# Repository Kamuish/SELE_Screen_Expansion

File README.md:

# SCREEN EXPANSION PROJECT

The purpose of this project is to make two screens work as a single one, with the screen coming out of
the rigth screen, entering the left one. After "leaving" the left screen it should loop back.

We created a library to work with the LCD1602A LCD display, using the SPI and I2C communication protocols.
Afterwards, we implemented EEPROM,FLASH and SRAM memory tests to verify the proper behaviour of those memories.

If one of those memories fails, program execution shall be halted and an error message will appear on one of the screens.

## Project structure:

We have 3 different folders:

  - Board - where the schematic and PCB design are stored;
  - src - where the code is;
  - docs - where the documentation is stored.
  
# src structure:
  
  Inside this folder we find many folders, each for a different purpose:
  
    - I2C - folder in which we have a program to show the I2C protocol during the presentation;
    - SPI - folder in which we have a program to show the SPI protocol during the presentation;
    - SRAM - folder used for development of the SRAM test;
    - eeprom_write_hash - project used to write the hash to the eeprom memory address;
    - flash_test - folder used for the development of the Flash memory test;
    - hash_calc - python script to calculate the hash of a IntelHex file;
    - screen_expansion_project - the final project.
# The screen_expansion_project

Inside this folder the header files are inside the Header Files folder and the program files inside the Program Files folder.

All the files are properly named and commented, simplifying the task of reading the project's source files.

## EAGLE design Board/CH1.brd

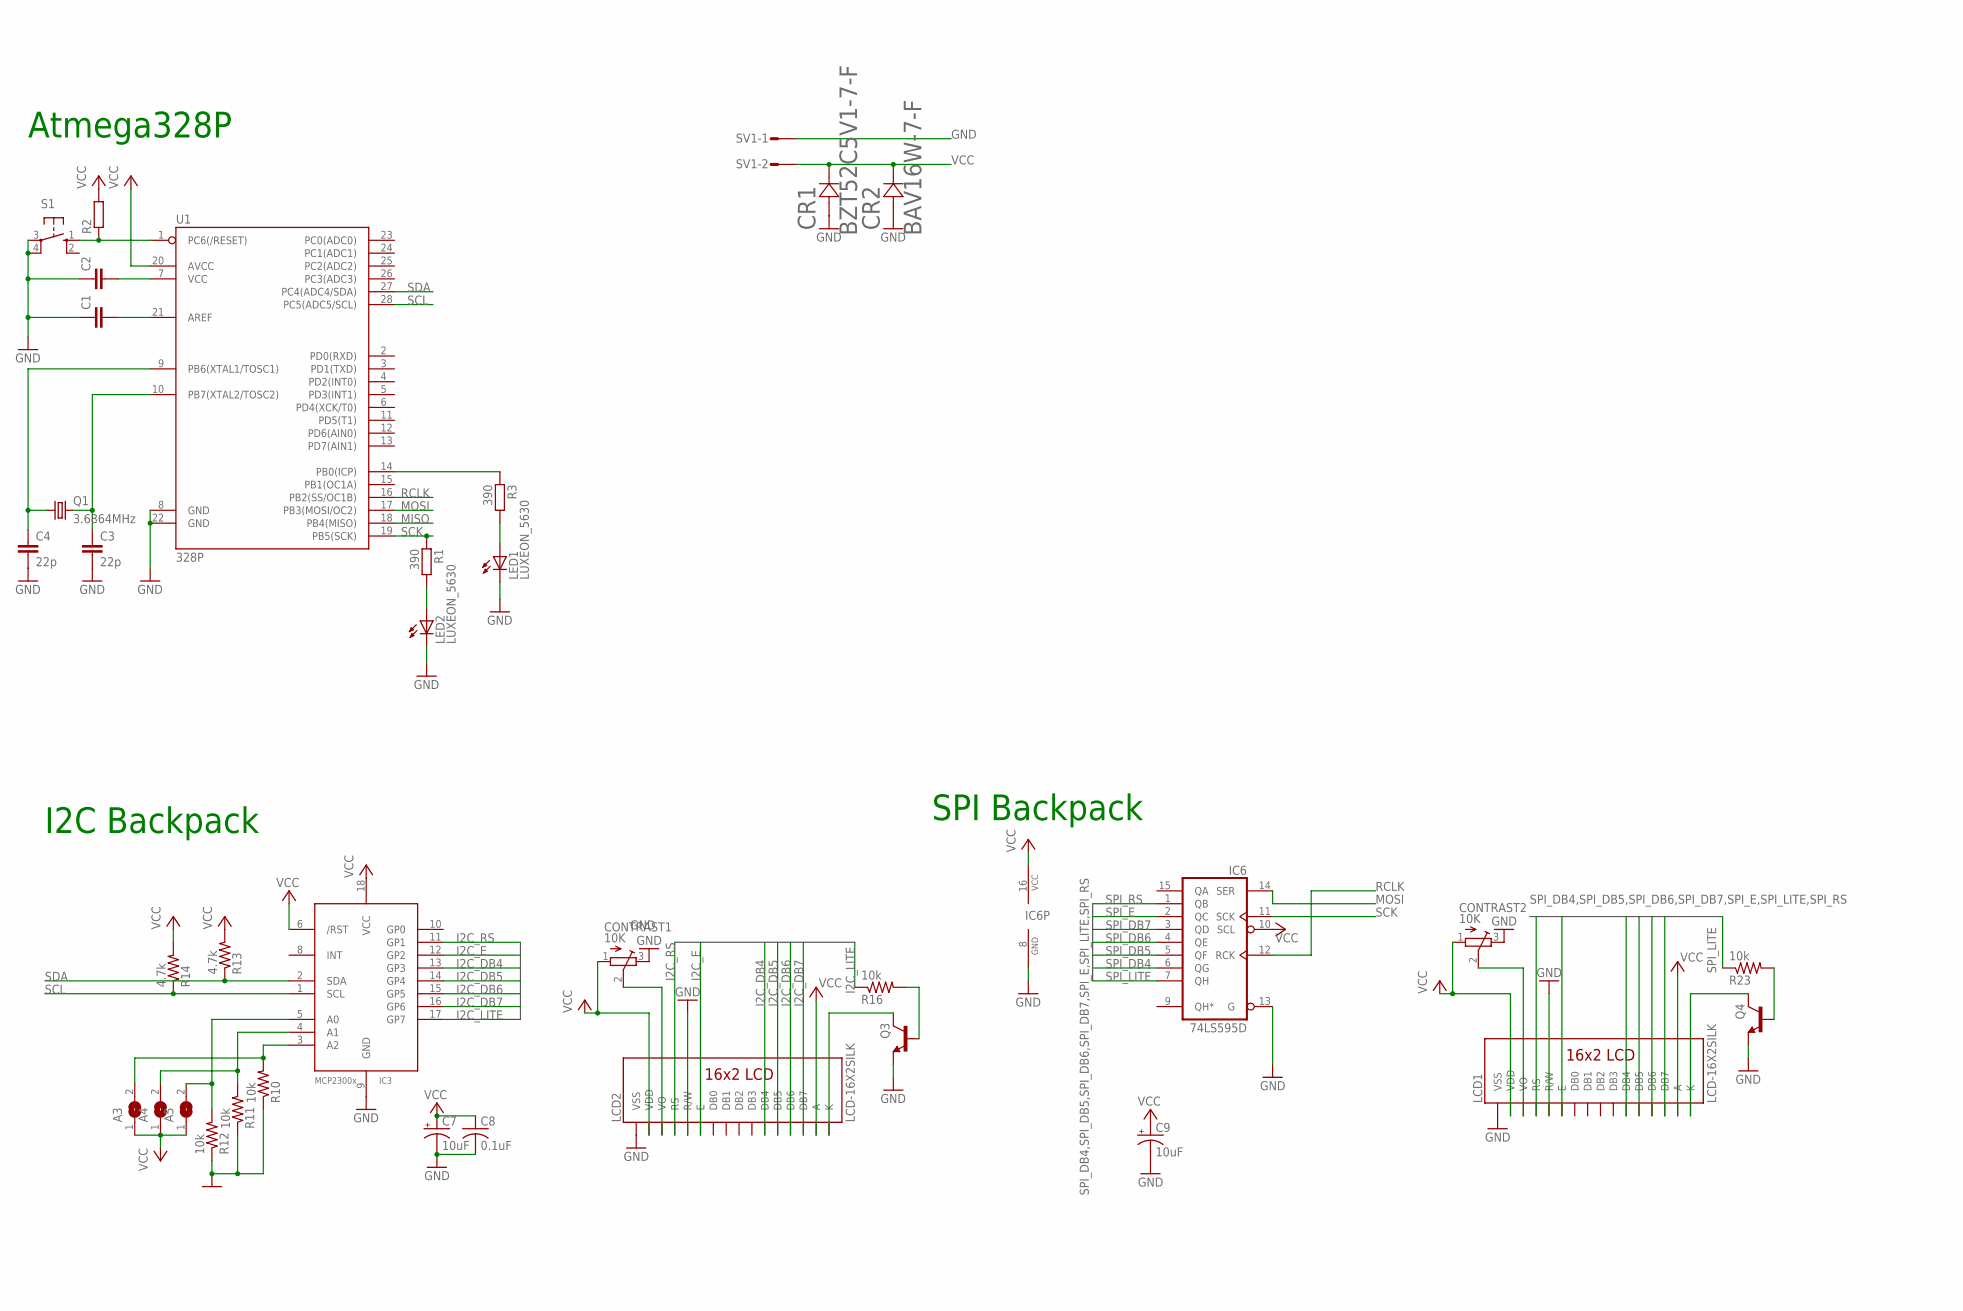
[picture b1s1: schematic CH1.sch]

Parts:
A3, A4, A5: SJ
C1, C2: C-EUC1206; C1206
C3, C4: 22p; C1206
C7, C9: 10uF; A/3216-18R
C8: 0.1uF; C0805K
CONTRAST1, CONTRAST2: 10K; TC33X
CR1: BZT52C5V1-7-F; SOD123
CR2: BAV16W-7-F; SOD123
IC3: MCP2300X/SO; SO18W
IC6: 74LS595D; SO16
LCD1, LCD2: LCD-16X2SILK; LCD-16X2
LED1, LED2: LUXEON_5630
Q1: 3.6864MHz; HC49/S
Q3, Q4: MMBT2222ALT1-NPN-SOT23-BEC; SOT23-BEC
R1, R3: 390; R1206
R2: R-EU_R1206; R1206
R10, R11, R12, R16, R23: 10k; R0805
R13, R14: 4.7k; R0805
S1: SWITCH-OMRON; SWITCH-OMRON_B3F-10XX
SV1: L02P
U1: 328P; MICROCONTROLLER_DIP28

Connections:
GND: C1.1, C2.1, C3.2, C4.2, C7.-, C8.2, C9.-, CONTRAST1.3 (E), CONTRAST2.3 (E), CR1.2 (21), CR2.2 (21), IC3.9 (GND), IC6.8 (GND), IC6.13 (G), LCD1.1 (VSS), LCD1.5 (R/W), LCD2.1 (VSS), LCD2.5 (R/W), LED1.1@1 (C), LED1.1@2 (C), LED2.1@1 (C), LED2.1@2 (C), Q3.E, Q4.E, R10.1, R11.1, R12.1, S1.3, S1.4 (P1), SV1.1, U1.8 (GND), U1.22 (GND)
I2C_DB4: IC3.13 (GP3), LCD2.11 (DB4)
I2C_DB5: IC3.14 (GP4), LCD2.12 (DB5)
I2C_DB6: IC3.15 (GP5), LCD2.13 (DB6)
I2C_DB7: IC3.16 (GP6), LCD2.14 (DB7)
I2C_E: IC3.12 (GP2), LCD2.6 (E)
I2C_LITE: IC3.17 (GP7), R16.1
I2C_RS: IC3.11 (GP1), LCD2.4 (RS)
MISO: U1.18 (PB4(MISO))
MOSI: IC6.14 (SER), U1.17 (PB3(MOSI/OC2))
unnamed: C3.1, Q1.2, U1.10 (PB7(XTAL2/TOSC2))
unnamed: C4.1, Q1.1, U1.9 (PB6(XTAL1/TOSC1))
unnamed: C2.2, U1.7 (VCC)
unnamed: C1.2, U1.21 (AREF)
unnamed: LED1.2 (A), R3.2
unnamed: LED2.2 (A), R1.2
unnamed: R2.1, S1.1 (S), U1.1 (PC6(/RESET))
unnamed: R3.1, U1.14 (PB0(ICP))
unnamed: A5.2, IC3.5 (A0), R12.2
unnamed: A4.2, IC3.4 (A1), R11.2
unnamed: A3.2, IC3.3 (A2), R10.2
unnamed: LCD2.16 (K), Q3.C
unnamed: Q3.B, R16.2
unnamed: CONTRAST1.2 (S), LCD2.3 (VO)
unnamed: LCD1.16 (K), Q4.C
unnamed: Q4.B, R23.2
unnamed: CONTRAST2.2 (S), LCD1.3 (VO)
RCLK: IC6.12 (RCK), U1.16 (PB2(SS/OC1B))
SCK: IC6.11 (SCK), R1.1, U1.19 (PB5(SCK))
SCL: IC3.1 (SCL), R14.1, U1.28 (PC5(ADC5/SCL))
SDA: IC3.2 (SDA), R13.1, U1.27 (PC4(ADC4/SDA))
SPI_DB4: IC6.6 (QG), LCD1.11 (DB4)
SPI_DB5: IC6.5 (QF), LCD1.12 (DB5)
SPI_DB6: IC6.4 (QE), LCD1.13 (DB6)
SPI_DB7: IC6.3 (QD), LCD1.14 (DB7)
SPI_E: IC6.2 (QC), LCD1.6 (E)
SPI_LITE: IC6.7 (QH), R23.1
SPI_RS: IC6.1 (QB), LCD1.4 (RS)
VCC: A3.1, A4.1, A5.1, C7.+, C8.1, C9.+, CONTRAST1.1 (A), CONTRAST2.1 (A), CR1.1 (12), CR2.1 (12), IC3.6 (/RST), IC3.18 (VCC), IC6.10 (SCL), IC6.16 (VCC), LCD1.2 (VDD), LCD1.15 (A), LCD2.2 (VDD), LCD2.15 (A), R2.2, R13.2, R14.2, SV1.2, U1.20 (AVCC)

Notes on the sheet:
Atmega328P
I2C Backpack
SPI Backpack

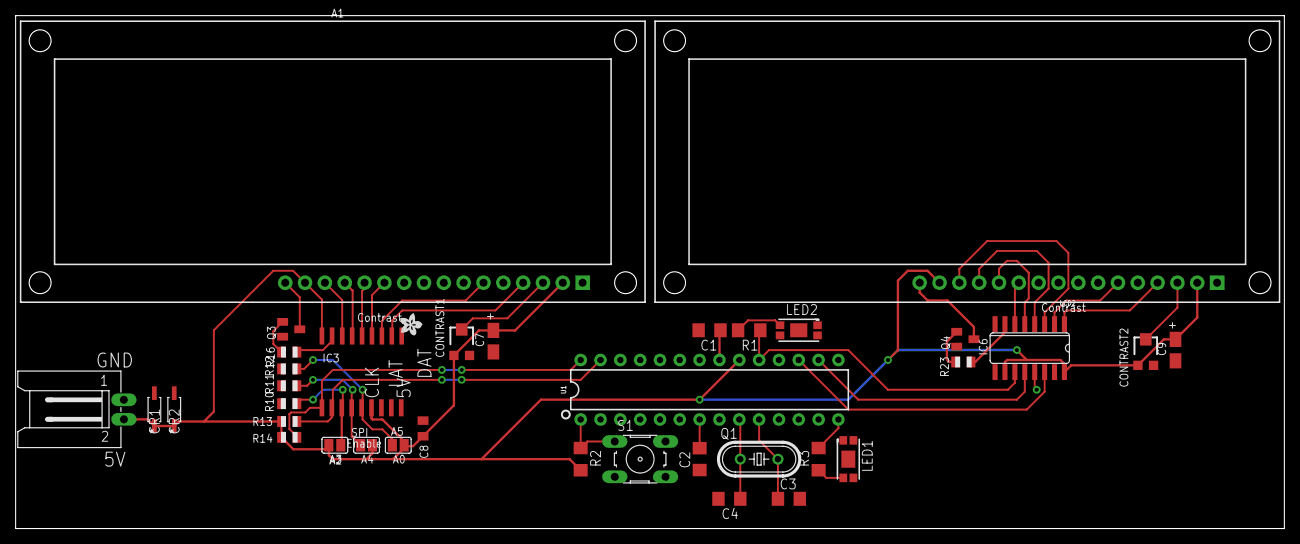
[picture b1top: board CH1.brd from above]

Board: 2 copper layers, 162.5 x 65.7 mm, 37 parts (0 on the bottom side), 38 nets.

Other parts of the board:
U$2: ADAFRUIT200MIL

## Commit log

2018-11-13 System diagram
2018-11-13 Gantt Chart
    Impossibru gantt chart
2018-11-24 Initial SPI commit.
2018-11-25 Initial I2C
2018-12-04 lcd datasheet
2018-12-06 Figured out SPI. Prints 'O' to first character, first line.
2018-12-08 Added screen interface library 'LCD1602A'. Allows to write one character at a time.
2018-12-08 Added functions to LCD library. Allows the writing of strings.
2018-12-08 Removed starting instructions (no need). Remaking 'screen_instruction' function to allow the use of datasheet commands.
2018-12-08 Re-added starting instructions.
2018-12-08 Detailed gantt chart
2018-12-08 Modified LCD functions to allow the use of instructions from the datasheet.
2018-12-10 structure of the repo
2018-12-10 Working version
2018-12-10 Working screen
2018-12-10 Applied DRY principle
2018-12-10 Screen instructions
2018-12-10 REadability
2018-12-10 Guidelines
2018-12-10 Screen library
2018-12-10 Removed redundant files
2018-12-10 Documentacao
2018-12-10 Updated Gantt chart
2018-12-11 Data types
2018-12-11 Tests with the screen library
2018-12-11 I2C library complete
2018-12-11 Instructions for includes
2018-12-11 Complete I2C interface
2018-12-11 gitignore
2018-12-11 Created project structure for final project. Import 'screen_expansion_project' with eclipse
2018-12-11 Structure changes
2018-12-11 rename
2018-12-11 SPI interface ??
2018-12-11 WOrking i2c
2018-12-11 Source file prologs
2018-12-11 working library.
2018-12-11 Removed renamed folders
2018-12-11 TYpo
2018-12-11 Added latest developments to the final project.
2018-12-12 POssible SPI fix?
2018-12-12 Nasa guidelines and documentation
2018-12-12 Screen share - alpha version
2018-12-12 Details
2018-12-13 Fixed main to not initialize SPI twice.
2018-12-13 Integrating SPI and I2C in the same file.
2018-12-14 State machine
2018-12-14 JPL rules
2018-12-14 Remove screen flicker
2018-12-14 Working version for undeer 16 word strings
2018-12-14 Almost complete version
2018-12-14 Working state machine
2018-12-14 MISRA compliance; Style guide compliance
2018-12-15 First commit of UART implementation for debugging purposes.
2018-12-15 Re-commiting UART library code.
2018-12-16 Writes the hash to eeprom addr
2018-12-16 Updated Gantt
2018-12-16 Initial commit of flash tests
2018-12-17 SRAM testing. MarchC test implemented.
2018-12-17 Working flash test
2018-12-17 Changes to state machine and Shift_Strings library to shift a string between the strings.
2018-12-17 Python hash calculator
2018-12-17 Removed unused version
2018-12-17 Removed redundant file
2018-12-17 README
2018-12-17 Misra
2018-12-17 Gantt updates
2018-12-17 Removed redundant folder
2018-12-17 re struct of repo
2018-12-17 Commented the State Machine and general changes to main.
2018-12-18 Organization of docs
2018-12-18 FLash tests
2018-12-18 Style guide
2018-12-18 Defensive programming
2018-12-18 Style
2018-12-18 Misra comments
2018-12-18 JPL code guide
2018-12-18 Removed repeated variable name
2018-12-18 Misra rule 6.5
2018-12-18 Default case
2018-12-18 Misra standards
2018-12-18 DOcumentation and def programming
2018-12-18 Adding SRAM test to main.c. Fixed a bug in the SRAM library.
2018-12-18 Removing extra files from merge
2018-12-18 Fixing files from merge.
2018-12-18 Removed some more extra files.
2018-12-18 Eeprom tests
2018-12-18 Docs
2018-12-18 corrected unexpected behaviour
2018-12-18 Removed UART protocol from production version
2018-12-18 Memory test libraries MISRA compliance.
2018-12-19 Code prepared for external Atmega328p.
2018-12-19 Bug fix in FLASH test. Integrating memory tests.
2018-12-19 Bugcorrection in eeprom_write
2018-12-19 Further bug corrections in eeprom_write_hash
2018-12-19 Changing address to write to eeprom
2018-12-19 check for errors on the I2C protocol
2018-12-19 Changes to EEPROM test. Memory tests now work as expected.
2018-12-19 Fixed bug
2018-12-19 Removed bug on boolean values
2018-12-19 I2C test project
2018-12-19 Fixed I2C interface
2018-12-19 Initialized output LED
2018-12-19 Updated version of I2C protocol
2018-12-19 Documentation
2018-12-20 Doducmentation
2018-12-20 Debugging programming of the Atmega328P
2018-12-20 DOCS2
2018-12-20 DOcumentação
2018-12-20 Presentation guidelines
2018-12-20 Renamed EEPROM write project
2018-12-20 Fixed import
2018-12-20 Demonstration of SPI protocol
2018-12-20 Added some points
2018-12-20 Fixed includes
2018-12-20 Project files
2018-12-20 Major bug correction. I2C error LED was bugging SPI to the point of breaking the application.
2018-12-20 Re-tested memory tests and the FLASH test seems to be broken.
2018-12-20 FIxed bug on handling NACK
2018-12-20 SPI DEMO
2018-12-20 Final commit before presentation. Fixed some bugs. Eveything working as expected.
2018-12-20 Oscilloscope prints
2018-12-26 Update SRAM_test.c
    Misra compliance
2018-12-26 Update FLASH_test.h
    Misra compliance
2018-12-26 Update LCD1602A.h
    Misra compliance
2018-12-26 Deleted uart protocol
2018-12-26 Update main.c
    Misra
2018-12-26 Misra compliance
2018-12-26 renamed images
2018-12-26 Changes to the board. Added all the components. Needs review and adjustments to improve quality.
2018-12-27 Changes to board, checked autorouter, via and trace size. ToDo: Check silk.
2018-12-28 Images for the report
2018-12-28 removed empty project
2018-12-28 removed UART communication
2018-12-28 Final version of the gantt chart

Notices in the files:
parts and their libraries:
led: Lumileds 5630 Datasheet DS201 20130228 ©2013 Philips Lumileds Lighting Company.
SparkFun-Displays: Licensing: Creative Commons ShareAlike 4.0 International - https://creativecommons.org/licenses/by-sa/4.0
